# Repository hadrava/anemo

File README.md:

# anemo
Datalogger hack for Anemometer Kaindl Windmaster 2

Status: Sensor board is working, no interresting code yet, sd-card board not designed yet

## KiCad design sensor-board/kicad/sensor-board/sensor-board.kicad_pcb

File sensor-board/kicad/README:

R7 funguje od cca 300R do desítek kOhmů...

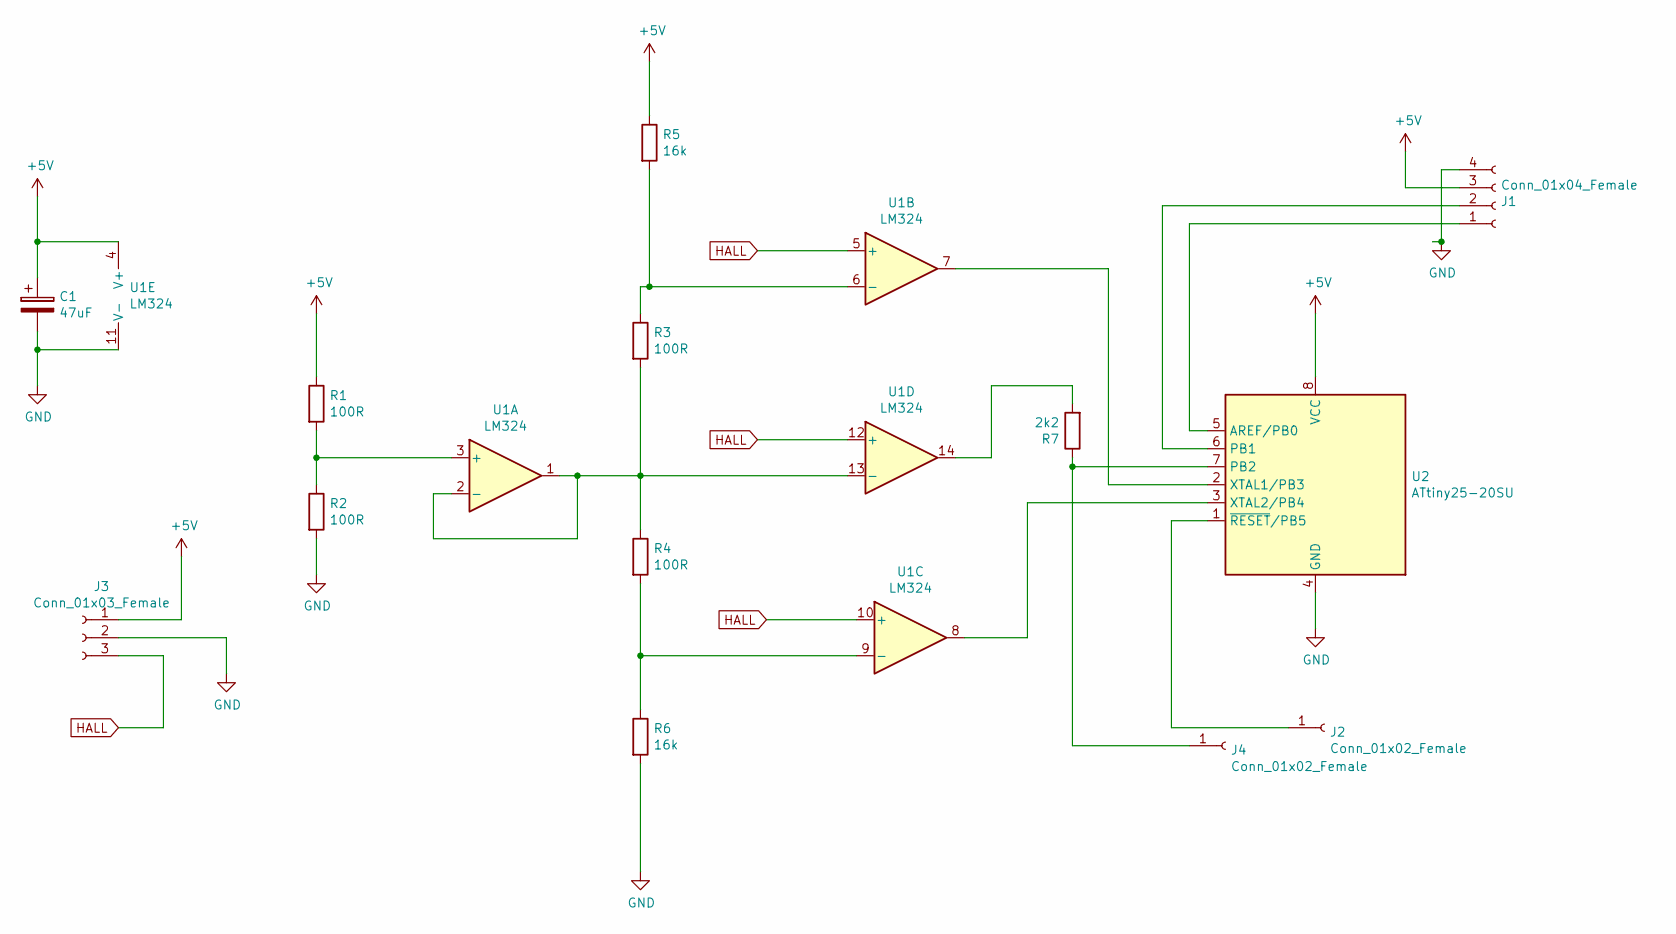
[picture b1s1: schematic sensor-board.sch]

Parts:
C1: 47uF; C_Radial_D5.0mm_H7.0mm_P2.00mm
J1: Conn_01x04_Female; PinSocket_1x04_P2.54mm_Vertical
J2, J4: Conn_01x02_Female; PinSocket_1x01_P2.54mm_Vertical
J3: Conn_01x03_Female; PinSocket_1x03_P2.54mm_Vertical
R1, R2, R3, R4: 100R; R_1206_3216Metric_Pad1.42x1.75mm_HandSolder
R5, R6: 16k; R_1206_3216Metric_Pad1.42x1.75mm_HandSolder
R7: 2k2; R_1206_3216Metric_Pad1.42x1.75mm_HandSolder
U1: LM324; DIP-14_W7.62mm
U2: ATtiny25-20SU; SOIJ-8_5.3x5.3mm_P1.27mm

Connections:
+5V: C1.1, J1.3, J3.1, R1.1, R5.1, U1.4 (V+), U2.8 (VCC)
GND: C1.2, J1.4, J3.2, R2.2, R6.2, U1.11 (V-), U2.4 (GND)
HALL: J3.3, U1.5 (+), U1.10 (+), U1.12 (+)
unnamed: J1.1, U2.5 (AREF/PB0)
unnamed: J1.2, U2.6 (PB1)
unnamed: J2.1, U2.1 (~RESET~/PB5)
unnamed: J4.1, R7.1, U2.7 (PB2)
unnamed: R1.2, R2.1, U1.3 (+)
unnamed: R3.1, R5.2, U1.6 (-)
unnamed: R3.2, R4.1, U1.1, U1.2 (-), U1.13 (-)
unnamed: R4.2, R6.1, U1.9 (-)
unnamed: R7.2, U1.14
unnamed: U1.7, U2.2 (XTAL1/PB3)
unnamed: U1.8, U2.3 (XTAL2/PB4)

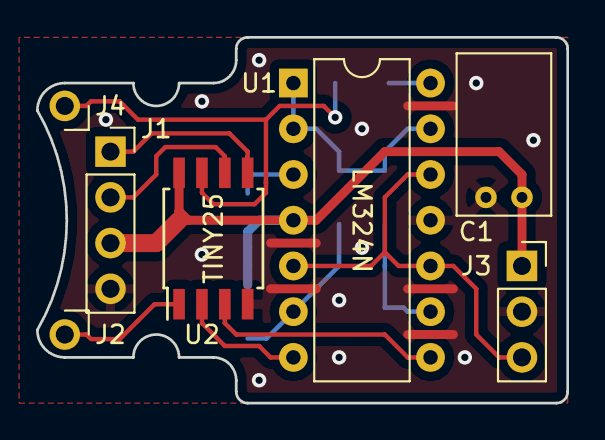
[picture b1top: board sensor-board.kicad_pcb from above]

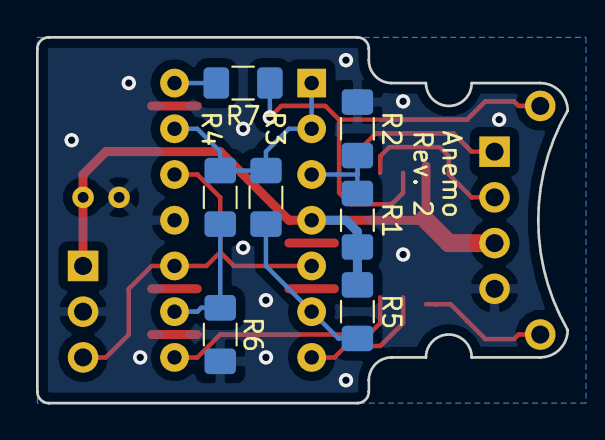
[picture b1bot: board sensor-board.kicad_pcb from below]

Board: 2 copper layers, 29.5 x 20.3 mm, 14 parts (7 on the bottom side), 14 nets.

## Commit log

2019-01-24 Sensor-board: První revize (odesláno k výrobě)
2019-02-20 Sensor-board: revize 2
    Opravená chyba: Operační zesilovač má silnější výstup než programátor,
    takže kompletně sestavená revize 1 nelze snadno flashnout.
2019-02-21 Sensor-board: testovací kód -- kopíruje skryté vstupy senzoru na RXD a TXD
